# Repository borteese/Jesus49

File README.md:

# Jesus49
49-key Ergonomic keyboard designed and created by me.
# Ingredients
(1) Arduino Micro (standard w/header pins)

(49) THT 1N4148 Zener Switching Diode

(40*3) Breakaway Header Pins 2.54mm male Right Angle Single Row

(120) Female to Female Jumper Wires Ribbon 2.54mm 6-12 inches

(1) PCB (I ordered from JLCPCB, they are quite affordable)

(1) USB-MICRO

(49) Mechanical Keyboard switch 5-pin pcb-mount of your choice (I chose Gateron Ink Blacks)

(3) PCB Screw In 2u Stabilizers (I chose Durock v2s)

**Optional** (15) 2mm screw diameter, can be your prefrence depending on how you make the case (if you even do).

Keycap description in Jesus49.json, https://Keyboard-layout-editor.com, in summary. 3u can be replaced with 2.75u. I used KAT BOW Keycaps dye-sub pbt.
# Tools
Soldering Iron
Lead-Tin solder (Thin wire)
# How To Cook
Download the Gerber Pcb file (Kbpcb49.zip). Buy the file from any preferable website that can print and fabricate pcbs. I chose JLCPCB. When buying the product, make sure in the viewer, there are little tabs on each pcb part, if not, try a different website. Also set layers to 2.

Now that you have your pcbs, snap them into the squares/shapes that they are meant to be.

Put one diode into one of the  diodes slots. The diode holes are marked with D#. Make sure the Cathode (should be marked on the diode with a black ring on one side) is on the sqare surface's side, anode on the circular side. Also make sure that the actual diode is not on the side where you put the switches, but on the other side. Bend the wires of the diode so it does not fall, and solder the thing. Repeat this process for every diode.

Break the header pins into their corrosponding slot amounts. Place the header pins in place. Idk which way just make them not be on the switch's side or else ur screwed lmao. Solder without messing up. Do this with the arduino mounting pcb with the pins facing outwards or else ur also screwd. solder the arduino in with the top on the side with # U1.

Connect everything with jumperwires to their corrosponding connections.

Using the Arduino IDE, https://www.arduino.cc/en/software, load the code I have attached (48KB.ino). Go to tools, board, and select arduino micro if not already. Connect your tging ti computer siong usb micro. Vertify. If everything is well (no error messages), upload the program. If everything is well and I am an actuall genius (which I doubt I am) then you can type and stuff press mode to siwtch to a different layer ok bye you are now keybord fanatic whno followed some stupid thing you should have more trust issues i swear people now n days trust everyting theyt se my je sus49 oj im going insae hapel.

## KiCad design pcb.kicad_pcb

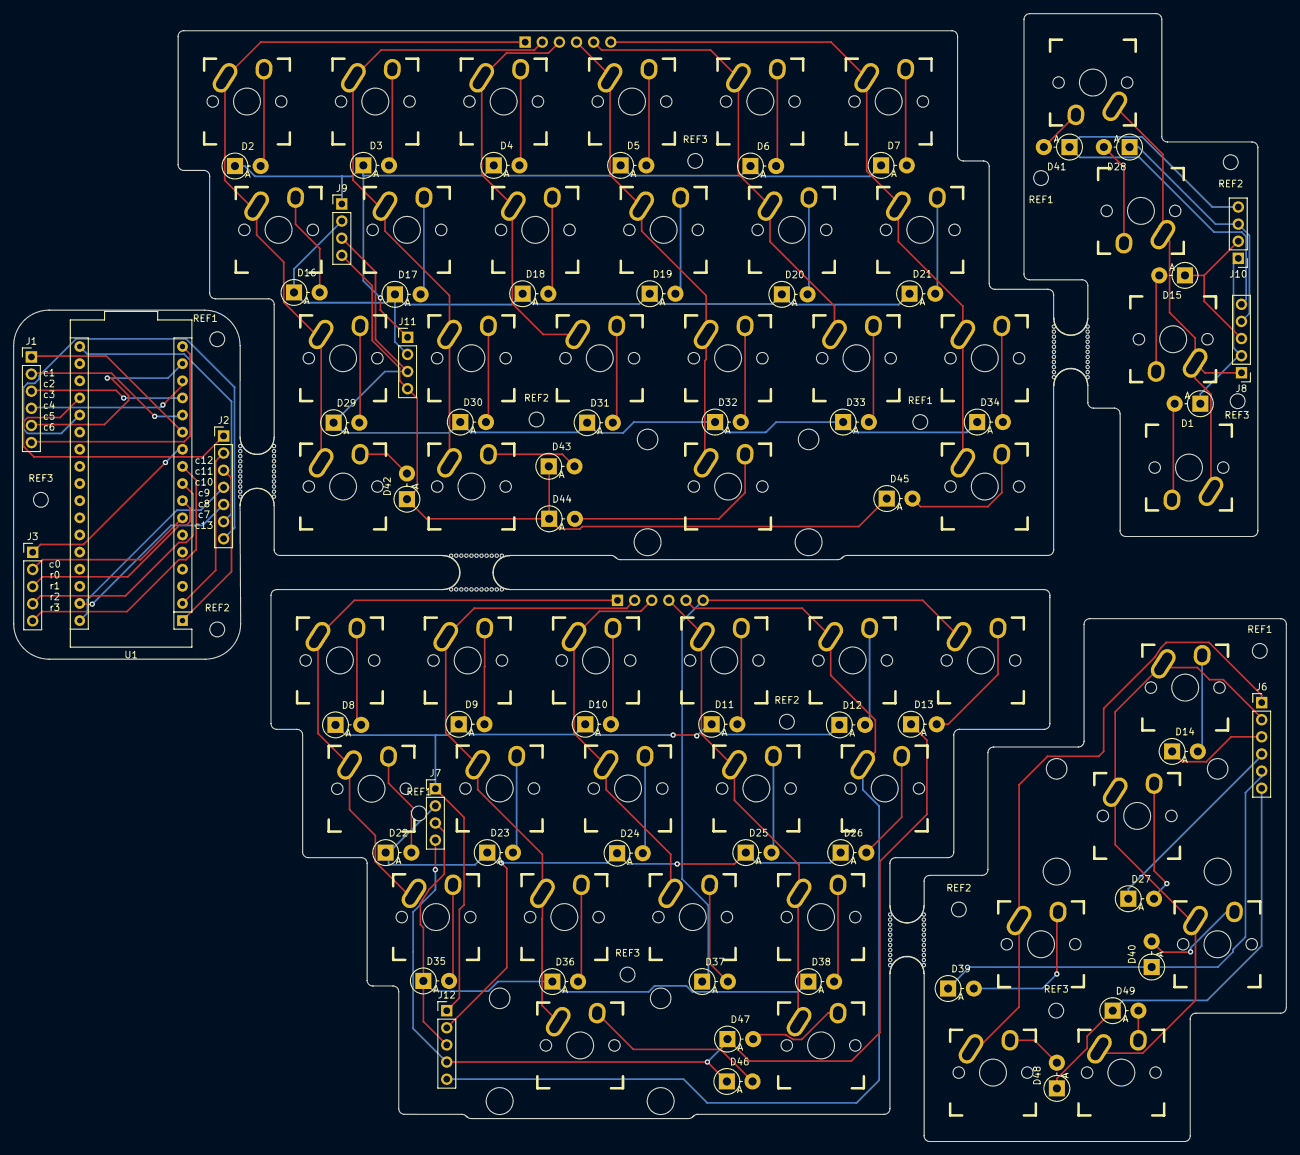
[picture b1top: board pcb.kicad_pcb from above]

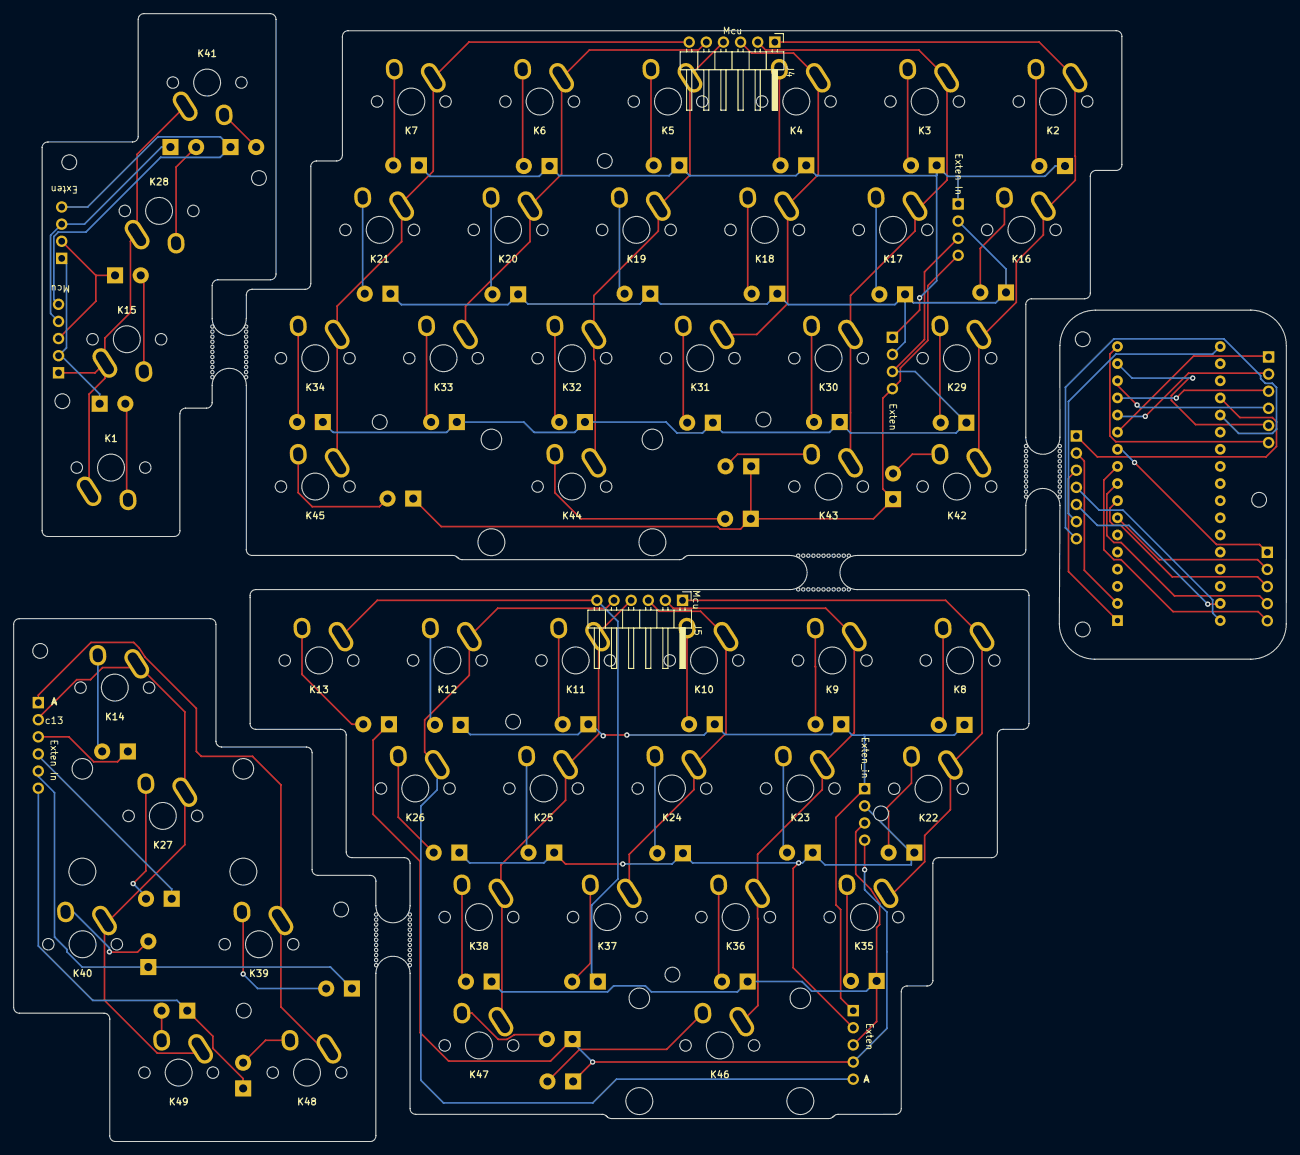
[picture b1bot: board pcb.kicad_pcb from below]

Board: 2 copper layers, 188.7 x 167.2 mm, 130 parts (2 on the bottom side), 98 nets.

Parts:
D1, D2, D3, D4, D5, D6, D7, D8, D9, D10, D11, D12, D13, D14, D15, D16, D17, D18, D19, D20, D21, D22, D23, D24, D25, D26, D27, D28, D29, D30, D31, D32, D33, D34, D35, D36, D37, D38, D39, D40, D41, D42, D43, D44, D45, D46, D47, D48, D49: D; D_DO-15_P3.81mm_Vertical_AnodeUp
J1, J6: Conn_01x06; PinHeader_1x06_P2.54mm_Vertical
J2: Conn_01x07; PinHeader_1x07_P2.54mm_Vertical
J3, J8, J12: Conn_01x05; PinHeader_1x05_P2.54mm_Vertical
J4, J5: Conn_01x06; PinHeader_1x06_P2.54mm_Horizontal
J7, J9, J10, J11: Conn_01x04; PinHeader_1x04_P2.54mm_Vertical
K1, K2, K3, K4, K5, K6, K7, K8, K9, K10, K11, K12, K13, K16, K17, K18, K19, K20, K21, K22, K23, K24, K25, K26, K29, K30, K31, K32, K33, K34, K35, K36, K37, K38, K40, K41, K42, K43, K45, K47, K48, K49: KEYSW; Mx_Alps_100
K14: KEYSW; Mx_Alps_150
K15: KEYSW; Mx_Alps_125
K27: KEYSW; Mx_Alps_225
K28, K39: KEYSW; Mx_Alps_175
K44, K46: KEYSW; Mx_Alps_275
REF1, REF1#2, REF1#3, REF1#4, REF1#5, REF2, REF2#2, REF2#3, REF2#4, REF2#5, REF3, REF3#2, REF3#3, REF3#4, REF3#5: MountingHole_2.2mm_M2
U1: Arduino_Micro
mouse-bite-5mm-slot, mouse-bite-5mm-slot#2, mouse-bite-5mm-slot#3, mouse-bite-5mm-slot#4: VAL**; mouse-bite-5mm-slot

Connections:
/a: J6.1, K39.1, K48.1
/col13: J6.2, K14.1, K27.1, K40.1, K49.1
/r0: D14.1, J6.3
/r1: D27.1, J6.4
/r2: D39.1, D40.1, J6.5
/r3: D48.1, D49.1, J6.6
unnamed: D1.1, J8.2, J10.1
unnamed: D1.2, K1.2
unnamed: D2.1, D3.1, D4.1, D5.1, D6.1, D7.1, J9.1, J11.1
unnamed: D2.2, K2.2
unnamed: D3.2, K3.2
unnamed: D4.2, K4.2
unnamed: D5.2, K5.2
unnamed: D6.2, K6.2
unnamed: D7.2, K7.2
unnamed: D8.2, K8.2
unnamed: D9.2, K9.2
unnamed: D8.1, D9.1, D10.1, D11.1, D12.1, J7.1, J12.1
unnamed: D10.2, K10.2
unnamed: D11.2, K11.2
unnamed: D12.2, K12.2
unnamed: D13.1, D46.1, D47.1, J7.4, J12.4
unnamed: D13.2, K13.2
unnamed: D14.2, K14.2
unnamed: D15.1, J8.3, J10.2
unnamed: D15.2, K15.2
unnamed: D16.1, D17.1, D18.1, D19.1, D20.1, D21.1, J9.2, J11.2
unnamed: D16.2, K16.2
unnamed: D17.2, K17.2
unnamed: D18.2, K18.2
unnamed: D19.2, K19.2
unnamed: D20.2, K20.2
unnamed: D21.2, K21.2
unnamed: D22.1, D23.1, D24.1, D25.1, D26.1, J7.2, J12.2
unnamed: D22.2, K22.2
unnamed: D23.2, K23.2
unnamed: D24.2, K24.2
unnamed: D25.2, K25.2
unnamed: D26.2, K26.2
unnamed: D27.2, K27.2
unnamed: D28.1, J8.4, J10.3
unnamed: D28.2, K28.2
unnamed: D29.1, D30.1, D31.1, D32.1, D33.1, D34.1, J9.3, J11.3
unnamed: D29.2, K29.2
unnamed: D30.2, K30.2
unnamed: D31.2, K31.2
unnamed: D32.2, K32.2
unnamed: D33.2, K33.2
unnamed: D34.2, K34.2
unnamed: D35.1, D36.1, D38.1, J7.3, J12.3
unnamed: D35.2, K35.2
unnamed: D36.2, K36.2
unnamed: D37.1, J5.6, K13.1
unnamed: D37.2, K37.2
unnamed: D38.2, K38.2
unnamed: D39.2, K39.2
unnamed: D40.2, K40.2
unnamed: D41.1, J8.5, J10.4
unnamed: D41.2, K41.2
unnamed: D42.1, D43.1, D44.1, D45.1, J9.4, J11.4
unnamed: D42.2, K42.2
unnamed: D43.2, K43.2
unnamed: D44.2, K44.2
unnamed: D45.2, K45.2
unnamed: D46.2, K46.2
unnamed: D47.2, K47.2
unnamed: D48.2, K48.2
unnamed: D49.2, K49.2
unnamed: J1.1, U1.12
unnamed: J1.2, U1.13
unnamed: J1.3, U1.14
unnamed: J1.4, U1.15
unnamed: J1.5, U1.16
unnamed: J1.6, U1.17
unnamed: J2.1, U1.21
unnamed: J2.2, U1.2
unnamed: J2.3, U1.1
unnamed: J2.4, U1.34
unnamed: J2.5, U1.33
unnamed: J2.6, U1.18
unnamed: J2.7, U1.22
unnamed: J3.1, U1.11
unnamed: J3.2, U1.7
unnamed: J3.3, U1.8
unnamed: J3.4, U1.9
unnamed: J3.5, U1.10
unnamed: J4.1, K2.1, K16.1, K29.1, K42.1
unnamed: J4.2, K3.1, K17.1, K30.1, K43.1
unnamed: J4.3, K4.1, K18.1, K31.1
unnamed: J4.4, K5.1, K19.1, K32.1, K44.1
unnamed: J4.5, K6.1, K20.1, K33.1
unnamed: J4.6, K7.1, K21.1, K34.1, K45.1
unnamed: J5.1, K8.1, K22.1, K35.1
unnamed: J5.2, K9.1, K23.1, K36.1, K46.1
unnamed: J5.3, K10.1, K24.1, K37.1
unnamed: J5.4, K11.1, K25.1, K38.1, K47.1
unnamed: J8.1, K1.1, K15.1, K28.1, K41.1
unnamed: J5.5, J12.5, K12.1, K26.1
